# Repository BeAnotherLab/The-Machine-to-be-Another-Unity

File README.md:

# The-Machine-to-be-Another-Unity

This is the repository for all things body swap with The Machine to be Another. Three different setups are supported. Manual body swap, Auto body swap, and Servo swap

### Servo swap

In this setup, the performer is copying the movements of the user, who is immersed in his body while listening to the story of the performer. This setup allows more freedom of movement for the user and more accuracy when copying movements.

Instructions on how to run the one-way swap can be found in [this pdf](https://github.com/BeAnotherLab/The-Machine-to-be-Another-Unity/blob/master/Files/The%20Machine%20to%20Be%20Another%20Protocols.pdf).

### Body swap

In this setup, usually shown in festivals as an installation both people are invited to synchronize with each other's movements. This is meant as a playful exploration of intimacy and empathy as explored in the original [gender swap](https://vimeo.com/84150219) video

Here is the equipment you need 

You can choose between Automatic swap (the software will automatically start and finish the experience, with audio instructions, based on some predefined timers and the detection of user presence) or Manual swap, where the whole experience is controlled from touchOSC.

- Install [Unity 2018.3.4f1] (https://unity3d.com/get-unity/download/archive)
- Install [Oculus Software](https://developer.oculus.com/downloads/)

- Clone this repository from GitHub: `git clone https://github.com/BeAnotherLab/The-Machine-to-be-Another-Unity.git`
- For the servo setup
- Install Arduino software
- Paste the ArduinoSerialCommand folder to your Arduino library folder
- Compile and upload the [Arduino control sketch](https://raw.githubusercontent.com/BeAnotherLab/The-Machine-to-be-Another-Unity/master/Arduino/ArduinoControl/ArduinoControl.ino) to the Arduino
- Open the project from Unity and run. Select the mode you want to use from the dropdown. When setting up the swap, enter the computer's IP in the input field and make sure only one of the two computers is set as repeater.
- All changes in settings are automatically saved  other 

## License

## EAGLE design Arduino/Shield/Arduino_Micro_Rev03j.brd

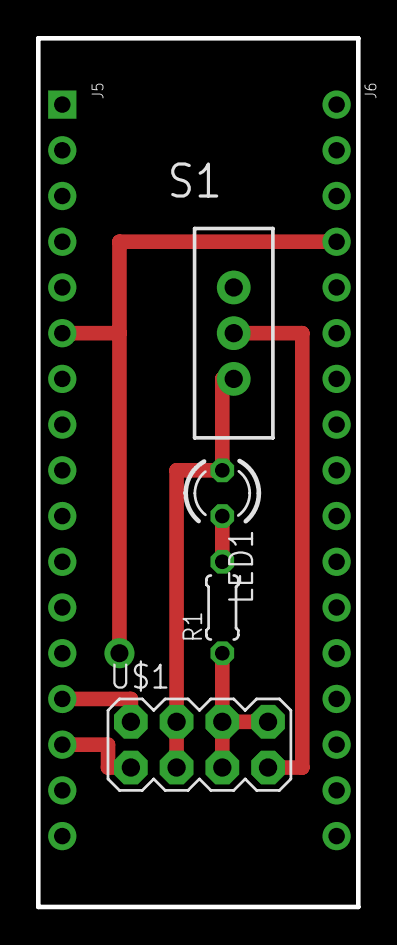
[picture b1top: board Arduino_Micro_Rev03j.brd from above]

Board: 2 copper layers, 17.8 x 48.3 mm, 6 parts (0 on the bottom side), 7 nets.

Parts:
J5: HEAD17-NOSS
J6: HEAD17-NOSS-1
LED1: LED3MM
R1: 0204/5
S1: SWITCH-SPDT
U$1: M04X2; 2X4

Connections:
BATT: LED1.A, S1.3, U$1.3, U$1.4
BATT_IN: S1.2, U$1.7
GND: J5.6, J6.4, R1.1, U$1.5, U$1.6, U$1.8
unnamed: LED1.K, R1.2
RESET: J5.5, J6.5
SERVO1: J5.14, U$1.2
SERVO2: J5.15, U$1.1

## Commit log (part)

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2025-07-03 comment out Android stuff in Uduino Manager editor
2025-07-03 Created Session State feature
2025-07-03 recover user presence functionality with session state feature. Not using events.
2025-07-04 scale up settings GUI
2025-07-04 remove wrongly added technorama scripts
2025-07-04 trying to recover custom player and custom network manager
2025-07-04 cleaning up and trying to recover settings based on previously working version
2025-07-04 connecting !
2025-07-07 remove rock vr and unused video feed
2025-07-07 upgrade avlive pro camera to version 2.9.3
2025-07-07 remove video consent scriptable object events
2025-07-07 cleaning up settings GUI
2025-07-07 remove unnecessary translations
2025-07-07 remove timeline dropdown
2025-07-07 show wait for serial message on startup when arduino mode?
2025-07-08 remove spark timelines
2025-07-08 remove spark audios
2025-07-08 remove diagrams that were stored in audio folders
2025-07-08 remove video capture prefabs
2025-07-08 remove plugins streaming assets
2025-07-08 remove streaming assets (translations and spark task structures)
2025-07-08 remove videoplayer helpers
2025-07-08 remove serizliable dictionary
2025-07-08 move plugins to third party assets folder
2025-07-08 fix settings gui scaling
2025-07-08 remove settings gui singleton
2025-07-08 remove audio manager instance
2025-07-08 audiomanager singleton removed (continued)
2025-07-16 Machine to be Another uno
2025-07-16 remove experiments docs
2025-07-18 cherry picking docs
2025-07-18 remove (all?) questionnaire stuff
    (cherry picked from commit c04e49751b8a911a866d28a88a3df81232912bed)
2025-07-18 remove csvmanager from scene
2025-07-18 disable event system in uduino interface
    (cherry picked from commit 5b843f15267e74043577d9883e452fb373872248)
2025-07-18 assign presence detection scriptable object variable?
2025-07-18 scale up settings GUI
    (cherry picked from commit 708d6a2609d60a7c2197fecfa9d9a9a8d28eae9b)
2025-07-18 remove references to rockvr video recorder
    (cherry picked from commit fba8b6cdf5a988040cfc659f82dc8ffbb61d448a)
2025-07-18 upgrade avlive pro camera to version 2.9.3
    (cherry picked from commit 1dd1a7b17e328d8b4a86474d7669998c2beaf2bc)
2025-07-18 remove curtain canvas
    (cherry picked from commit e713e5ae0db26fe6b3031f5e8daf56ff8af8d12a)
2025-07-18 recover settings gui
2025-07-21 use synchronized state instead of idle to allow presence detection to work with Vive and Quest link alike
2025-07-21 ignore logs
2025-07-21 remove osc manager singleton
2025-07-21 remove status manager instance
2025-07-21 remove display mode singleton
2025-07-22 update technorama flow
2025-07-22 reover session state feature
2025-07-22 use events to initialize instructions gui
2025-07-22 tryig to clean up autobodyswap instructions GUI setup
2025-07-22 more accurate technorama flow
2025-07-23 fix confirmation button regression
2025-07-23 clean up video feed script. switch dim button initial state
2025-07-23 remove audio sources from language pickers
2025-07-23 formatting whatevs
2025-07-23 remove audio manager from auto body swap scene
2025-07-23 rename instructions text bodyswap logic
2025-07-23 cleaning up. made images fadeable with canvas group. method not implemented yet
2025-07-24 wait for serial before stanbdy. clean up arduino and status manager
2025-07-25 Send serial status over OSC
2025-07-25 handle serial failure message
2025-07-25 session state keeps getting removed
2025-07-25 hide images if leaving during instructions
2025-07-25 let language buttons self manage their state
2025-07-25 fix bangage luttons
2025-07-25 initialize and reset with german
2025-07-25 change panomat shader (was only displaying in one eye)
2025-07-31 synchronized is the trigger state for vive pro 2
2025-07-31 remove graphy
2025-07-31 graphy on bottom right
2025-07-31 recovered camera index saving functionality
2025-08-13 reimport mirror why
2025-08-13 make instruction time line privat e
2025-08-13 decouple playable director from status manager
2025-08-14 remove useless docs
2025-08-15 add it to the scene
2025-08-15 reorder private and public methods
2025-08-15 remove unnecessary methods and group htem under self/other state changed
2025-08-15 remove consent variables
2025-08-15 remove experiencestarted/ended soo events. turned into a delegate to subscribe to from status manager
2025-08-15 finish moving user state managerment to its own manager. separate concerns
2025-08-15 finished separating
2025-08-15 remove standby SO event listeners
2025-08-15 missing ref to SO experiencetunning. remove unnecessary code
2025-08-15 this user left also stops the timelein
2025-08-18 don't hide panel from status manager
2025-08-18 rename methods. Separate wall off and mirror off
2025-08-18 was misdisassigning
2025-08-18 update lean localization
2025-08-18 exportt translations to csv
2025-08-19 generated audios
2025-08-19 move instructions textures
2025-08-19 add modern ui pack and textmeshpro to project
2025-08-19 updated specs
2025-08-19 add instrutions image to content
2025-08-19 add background and font
2025-08-19 update language buttons
2025-08-19 added french and italian translations
2025-08-19 Use Content Path
2025-08-19 sequence loadin
2025-08-20 creating new button materials
2025-08-20 convert them to json
2025-08-20 fix buttons
2025-08-20 update specs
2025-08-20 remove logging from loader
2025-08-20 are we sequencin
2025-08-20 we sequencing
2025-08-20 set language
2025-08-20 convert to ogg
2025-08-21 loading texts, added blank key
2025-08-21 trying to sequence load and show videos and images
2025-08-21 was missing SOO event and texture changes
2025-08-21 working mostly. sequence is no longer fit for swap. isuses with video loading time and hiding and showing to close to another.
2025-08-22 Hide panel
2025-08-22 load flag buttons
2025-08-22 use text mesh pro
2025-08-22 load font color
2025-08-22 hmm confirmatoin button
2025-08-22 Text mesh pro
2025-08-22 using unlit/texture shader for video feed
2025-08-22 no, this material is better
2025-09-01 make background white
2025-09-01 enable 2d ui
2025-09-01 add sdf font asset
2025-09-01 Revert "add sdf font asset"
    This reverts commit d4c085f76fdfecdbe5858ac87f90b566b0a5bfeb.
2025-09-01 i said bold
2025-09-01 yes really
2025-09-01 enable audio
2025-09-01 try performance boost
2025-09-02 don't use session state feature no more
2025-09-02 add end audio in mp3 remove other mp3 files
2025-09-02 simplify
2025-09-02 monitor height
2025-09-02 set height range
2025-09-02 threshold up
2025-09-02 destroy arduino manager when no serial control
2025-09-02 Revert "destroy arduino manager when no serial control"
    This reverts commit 2ec79b4a9b5a0ec1caf9edc9f8962d74a098d167.
2025-09-02 softer way to disable serial
2025-09-02 fix wall and mirror commands life cycle
2025-09-02 multi pass render mode for unlit fade shader
2025-09-02 wait then standby upon serial ready. was sending wrong user state value
2025-09-02 loop audio
2025-09-02 sidechaining music to instructions
2025-09-02 edit sequence.json first time
2025-09-03 downgrade
2025-09-03 fix end audios
2025-09-03 grid shader
2025-09-03 grid
2025-09-03 fade as we enter the area
2025-09-03 upside down
2025-09-03 initial position for 53
2025-09-03 show bounds before exiting them
2025-09-03 video
2025-09-03 tweaky
2025-09-03 cubic easing
2025-09-03 kill tweens properly
2025-09-03 rename
2025-09-03 bug was due to gazeonmultiplier value
2025-09-04 must show panel
2025-09-04 properly start with german
2025-09-04 boundaruy size
2025-09-04 bit higher
2025-09-04 try to force exposure
2025-09-05 add increment
2025-09-05 hide reticle on user ready
2025-09-05 try buttons
2025-09-05 recover play area dimensions
2025-09-05 remove camera icon that wss blocking build
2025-09-12 tweak sequence
2025-09-18 remove serial stuff
2025-09-18 remove unused elements
2025-09-18 reorder settings gui prefab eleents
2025-09-18 remove references to serial in status manager and start directly in standby
2025-09-18 remove regions in osc manager
2025-09-19 recover old manual body seap instruction gui
2025-09-19 recovered intro instructions
2025-09-19 add polish flag button
2025-09-19 added polish translations
2025-09-19 tidy up scripts
2025-09-19 add manual camera and en pl timeline
2025-09-22 add polish welcome instructions to timeline
2025-09-22 apply compressor to auidos
2025-09-22 re import mirror
2025-09-22 remove extOSC
2025-09-23 gotta use lean localized. remove language index
2025-09-23 remove crappy english instructions
2025-09-25 Refactor UserStateManager to use session state feature for headset detection
    Removed area-based area detection for headset presence and replaced it with session state checks in Update(). This change currently supports Rift CV1 only and simplifies user state management by dire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
2025-09-26 set text black
2025-09-26 must use "Main Camera" object name in manual scene too
2025-09-26 name set
2025-09-26 disable hot swap support
2025-09-26 ref camera for yaw recenter
2025-09-26 set repeater on startup
2025-09-26 wait and set polish
2025-09-26 make manual swap confirmation button and show it on start
2025-09-29 dont reset to german on standby
2025-09-29 properly reset on standby. remove faulty instructions timeline handler. no need for experience running scriptable object
2025-09-29 apply language changes
2025-09-29 hide image on removing headset during the instructions
2025-09-29 enable music
2025-09-30 wasnt setting experience runnign to true in other ready event
2025-09-30 rename timeline controller (typo in name)
2025-09-30 reformat audio manager to use events to sidechain background music instead of directly accessing it. Missing sidechain out at the end of the instructions
2025-10-02 dont play on awake
2025-10-08 tweak the idle screen
2025-12-10 create dummy spanish (polish) audios. create spanish translations
2025-12-10 create spanish button (temporary icon), no longer default to polish
2025-12-10 better ES flag
2025-12-11 final flag
2025-12-11 add spanish instructions audios and to the timeline
2025-12-11 assign spanish audios
2025-12-11 disabled grid layout group to put goodbye button
2025-12-11 fix translations
2025-12-11 created material for the spanish flag
2026-01-16 remove lean tween
2026-01-19 clean up audio files
2026-01-19 converted audios to ogg
2026-01-19 remove missing prefab confirmation button from auto swap
2026-01-19 removed something from manual swap scene
2026-01-19 move sequence data SO
2026-01-19 remove flag textures
2026-01-19 adding translation and flags
2026-01-20 tidy up
2026-01-20 add spanish translations json
2026-01-20 dunno
2026-01-20 create translations container
2026-01-20 churned out translations with gpt
2026-01-22 also assign language code to button so that it triggers correct event
2026-01-22 clean up swapcontrol gui to do only audio instructions
2026-01-22 Load through data loader and pass the clip to the audiomanager to play audio instructions (needs proper testing)
2026-01-23 remove manual swap instructions guI. there is only one instructions gui now. add it to the manual scene
2026-01-23 missing references to sequence data. fix selected languages key in config.json
2026-01-26 upgdate docs pdf
2026-01-26 update touch osc layout
2026-01-26 add mirror instruction on tablet and desktop ui
2026-01-26 fix instructions
2026-01-28 add stl mount models
2026-02-02 Remove Static and Sequence folders. Add Image Font and Config folders. rename folder to singular
2026-02-02 updated instructions layout for touch OSC and add bonus audio option on /btn7
2026-02-03 add audio instructions specs
2026-02-04 French Audio
2026-02-09 finalize control layout
2026-02-09 fix french translations
2026-02-09 remove panel loader because red border works better with insrtuction video. match audios to text description. use english and french
2026-02-09 re enable genderswap music
2026-02-09 stop instructions playback on sequence stopping
2026-02-09 typo
2026-02-09 don't use dotween sequence end callback to set exprience running variable value. this way we can display "other left" message.

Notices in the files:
parts and their libraries:
SparkFun-Electromechanical: Licensing: Creative Commons ShareAlike 4.0 International - https://creativecommons.org/licenses/by-sa/4.0
